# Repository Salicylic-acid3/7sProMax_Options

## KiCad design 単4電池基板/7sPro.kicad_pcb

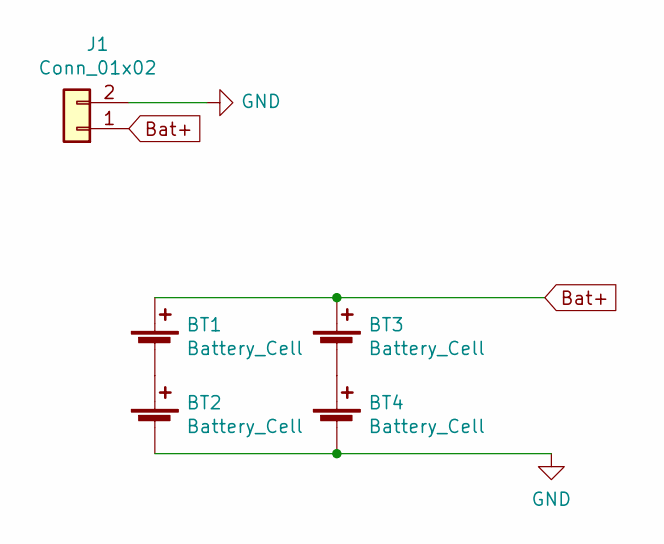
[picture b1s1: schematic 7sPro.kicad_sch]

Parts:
BT1, BT2, BT3, BT4: Battery_Cell
J1: Conn_01x02

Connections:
Bat+: BT1.1 (+), BT3.1 (+), J1.1
GND: BT2.2 (-), BT4.2 (-), J1.2
unnamed: BT1.2 (-), BT2.1 (+)
unnamed: BT3.2 (-), BT4.1 (+)

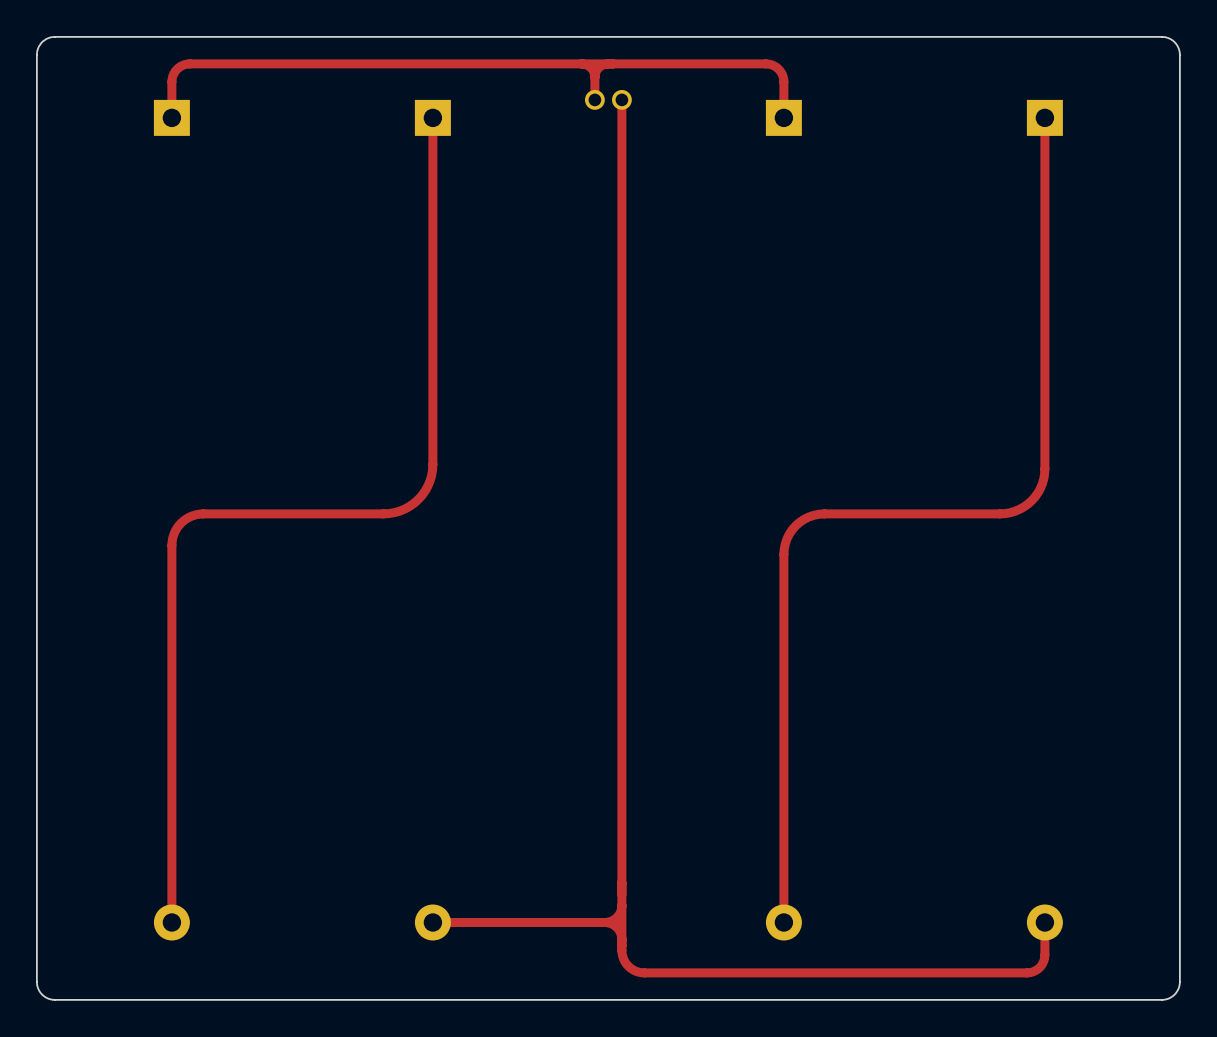
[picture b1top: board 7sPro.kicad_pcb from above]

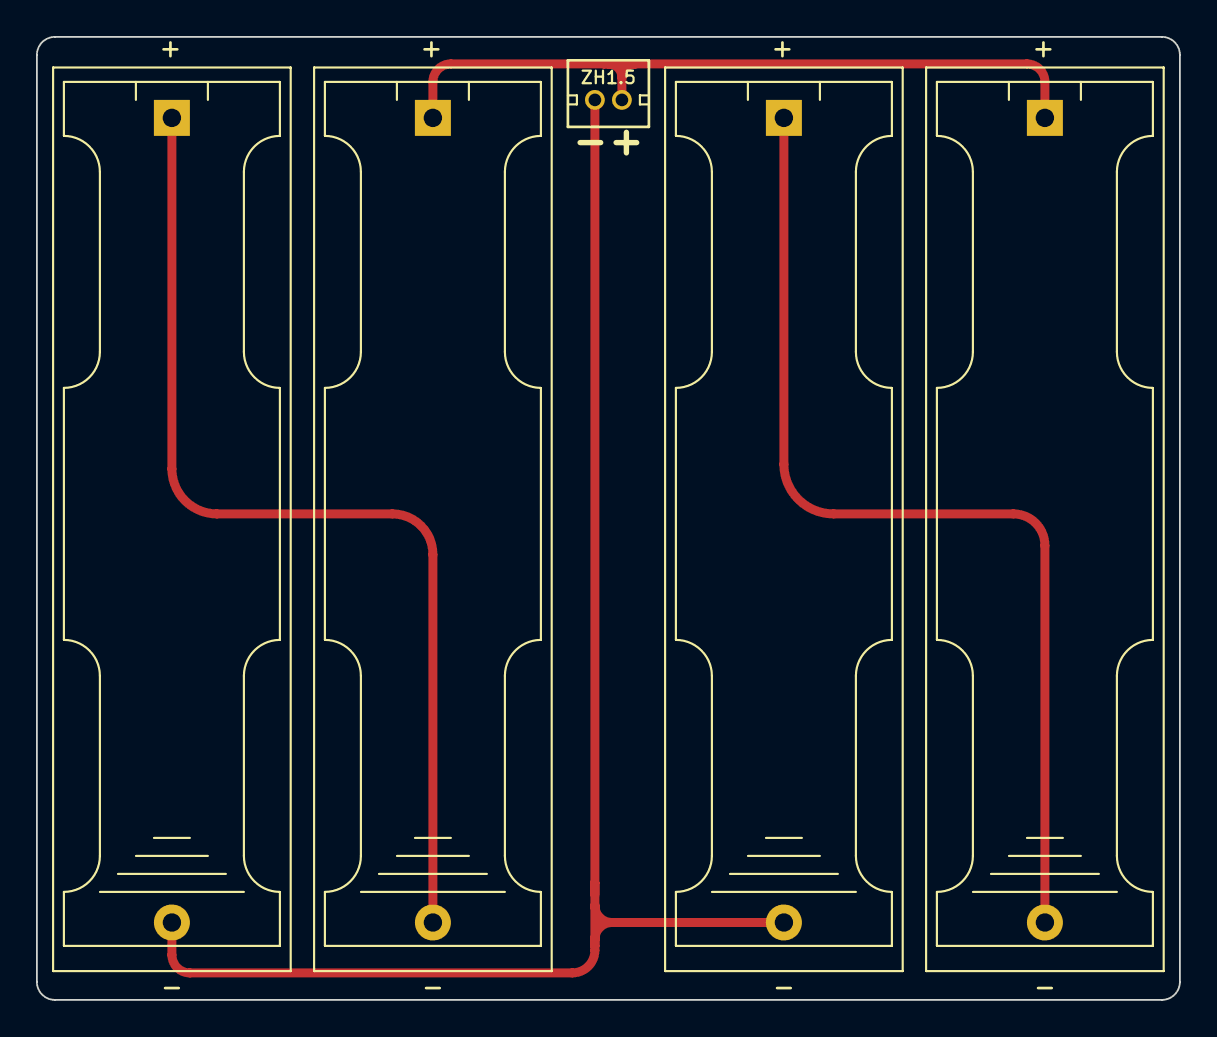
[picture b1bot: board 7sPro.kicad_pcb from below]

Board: 2 copper layers, 63.5 x 53.5 mm, 5 parts (4 on the bottom side), 4 nets.

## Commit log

2025-11-23 色々追加
